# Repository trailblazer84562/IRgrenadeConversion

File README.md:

# IRgrenadeConversion
Retrofit for using Recoil IR Grenade with LazerTag system

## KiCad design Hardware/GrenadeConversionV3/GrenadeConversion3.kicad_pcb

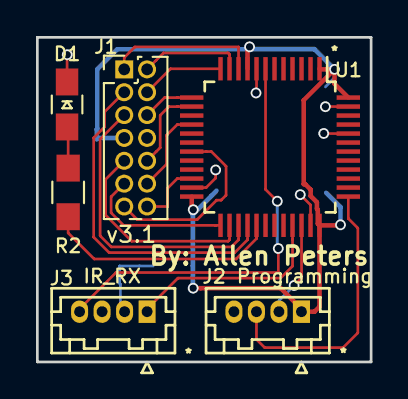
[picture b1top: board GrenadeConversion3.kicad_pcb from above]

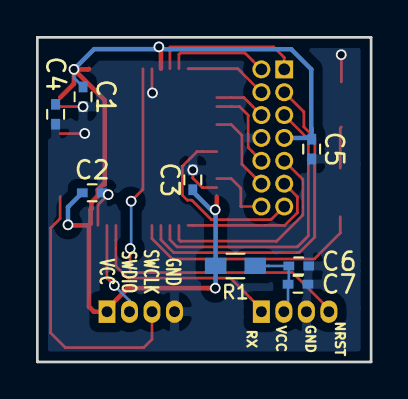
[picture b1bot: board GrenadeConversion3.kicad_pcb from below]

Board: 2 copper layers, 18.5 x 18.0 mm, 14 parts (8 on the bottom side), 21 nets.

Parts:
C1, C2, C3, C4: 0.1uF; C_0402
C5, C6, C7: 2.2uF; C_0402
D1: LED; C_0805_HandSoldering
J1: Grenade; Pin_Header_Straight_2x07_Pitch1.27mm
J2: Programming; Hirose_DF13-04P-1.25DSA_04x1.25mm_Straight
J3: IR_RX; Hirose_DF13-04P-1.25DSA_04x1.25mm_Straight
R1: 100; R_0603_HandSoldering
R2: R; R_0805_HandSoldering
U1: STM32F070CBTx; LQFP-48_7x7mm_Pitch0.5mm

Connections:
/Button_L: J1.13, U1.19
/IR_LED1: J1.1, U1.10
/IR_LED2: J1.3, U1.28
/IR_LED3: J1.5, U1.27
/IR_LED4: J1.9, U1.26
/IR_LED5: J1.10, U1.14
/IR_LED6: J1.6, U1.13
/IR_LED7: J1.4, U1.12
/IR_LED8: J1.2, U1.11
/IR_MOD_Out: J1.12, U1.16
/NRST: J3.4, U1.7
/Power: J1.11, U1.25
/RX: J3.1, U1.33
/SWCLK: J2.3, U1.37
/SWDIO: J2.2, U1.34
/greenLED: J1.14, U1.22
GND: C1.2, C2.2, C3.2, C4.2, C5.2, C6.2, C7.2, D1.1, J1.8, J2.4, J3.3, U1.8, U1.23, U1.35, U1.44, U1.47
unnamed: C6.1, C7.1, J3.2, R1.1
unnamed: D1.2, R2.2
unnamed: R2.1, U1.29
VCC: C1.1, C2.1, C3.1, C4.1, C5.1, J1.7, J2.1, R1.2, U1.1, U1.9, U1.24, U1.36, U1.48

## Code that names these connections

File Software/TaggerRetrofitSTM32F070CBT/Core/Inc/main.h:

/* USER CODE BEGIN Header */
/**
  ******************************************************************************
  * @file           : main.h
  * @brief          : Header for main.c file.
  *                   This file contains the common defines of the application.
  ******************************************************************************
  * @attention
  *
  * <h2><center>&copy; Copyright (c) 2020 STMicroelectronics.
  * All rights reserved.</center></h2>
  *
  * This software component is licensed by ST under BSD 3-Clause license,
  * the "License"; You may not use this file except in compliance with the
  * License. You may obtain a copy of the License at:
  *                        opensource.org/licenses/BSD-3-Clause
  *
  ******************************************************************************
  */
/* USER CODE END Header */

/* Define to prevent recursive inclusion -------------------------------------*/
#ifndef __MAIN_H
#define __MAIN_H

#ifdef __cplusplus
extern "C" {
#endif

/* Includes ------------------------------------------------------------------*/
#include "stm32f0xx_hal.h"

/* Private includes ----------------------------------------------------------*/
/* USER CODE BEGIN Includes */

/* USER CODE END Includes */

/* Exported types ------------------------------------------------------------*/
/* USER CODE BEGIN ET */

/* USER CODE END ET */

/* Exported constants --------------------------------------------------------*/
/* USER CODE BEGIN EC */

/* USER CODE END EC */

/* Exported macro ------------------------------------------------------------*/
/* USER CODE BEGIN EM */

/* USER CODE END EM */

void HAL_TIM_MspPostInit(TIM_HandleTypeDef *htim);

/* Exported functions prototypes ---------------------------------------------*/
void Error_Handler(void);

/* USER CODE BEGIN EFP */

/* USER CODE END EFP */

/* Private defines -----------------------------------------------------------*/
#define IR_LED1_Pin GPIO_PIN_0
#define IR_LED1_GPIO_Port GPIOA
#define IR_LED8_Pin GPIO_PIN_1
#define IR_LED8_GPIO_Port GPIOA
#define IR_LED7_Pin GPIO_PIN_2
#define IR_LED7_GPIO_Port GPIOA
#define IR_LED6_Pin GPIO_PIN_3
#define IR_LED6_GPIO_Port GPIOA
#define IR_LED5_Pin GPIO_PIN_4
#define IR_LED5_GPIO_Port GPIOA
#define IR_MOD_Out_Pin GPIO_PIN_6
#define IR_MOD_Out_GPIO_Port GPIOA
#define Button_L_Pin GPIO_PIN_1
#define Button_L_GPIO_Port GPIOB
#define greenLED_Pin GPIO_PIN_11
#define greenLED_GPIO_Port GPIOB
#define PowerCtrl_Pin GPIO_PIN_12
#define PowerCtrl_GPIO_Port GPIOB
#define IR_LED4_Pin GPIO_PIN_13
#define IR_LED4_GPIO_Port GPIOB
#define IR_LED3_Pin GPIO_PIN_14
#define IR_LED3_GPIO_Port GPIOB
#define IR_LED2_Pin GPIO_PIN_15
#define IR_LED2_GPIO_Port GPIOB
#define HeartbeatLED_Pin GPIO_PIN_8
#define HeartbeatLED_GPIO_Port GPIOA
#define RX_Pin GPIO_PIN_12
#define RX_GPIO_Port GPIOA
/* USER CODE BEGIN Private defines */
#define IR_RX_SENSOR_TICKS_GAVE_UP  10000
/* USER CODE END Private defines */

#ifdef __cplusplus
}
#endif

#endif /* __MAIN_H */

/************************ (C) COPYRIGHT STMicroelectronics *****END OF FILE****/

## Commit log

2020-10-24 Initial Upload
2020-10-24 Added emitTag
2020-10-26 added StartLEDFlash
    need more details for the queue's parameters
2020-12-15 Working Code - needs button monitor for shutdown
2020-12-19 Added button monitor for shutdown
2020-12-19 Add pull-up to button input - allow testing outside grenade body
2020-12-19 Update HW to V3.1 - Layout changes for easier manufacturing
2021-07-10 Added timeout for programming that shuts down the grenade
